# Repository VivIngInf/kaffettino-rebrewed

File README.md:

# ☕ Kaffettino Rebrewed (v2.0)

> Sistema embedded NFC per la gestione automatizzata delle consumazioni, progettato per ambienti reali e scalabilità.

## ☀️ "Buongiornissimo... Arrikaffè!?!?!"

Kaffettino Rebrewed è la **nuova generazione del [progetto Kaffettino](https://github.com/VivIngInf/VivereKaffettino)**: non un semplice aggiornamento, ma una **riscrittura completa** pensata per essere più efficiente, robusta e pronta al futuro.

Se la prima versione era un prototipo brillante, questa è la sua evoluzione:
**hardware custom**, software **modulare** e una filosofia più **industriale**.

## ☕ Cos'è Kaffettino?

Vivere Kaffettino è una **suite** che permette agli utenti dell’Università di Palermo, appartenenti a Vivere Ingegneria, di **segnare le proprie consumazioni** (non solo di caffè) in modo semplice e veloce.

Il sistema è basato su un **ESP32 con lettore NFC**:

- L’utente avvicina la propria card
- Viene verificato il saldo
- Il costo del caffè viene scalato automaticamente

La ricarica viene poi gestita da un amministratore.

## 🤔 Cos’è cambiato con Rebrewed?

Kaffettino Rebrewed nasce come una **reingegnerizzazione completa** del [progetto originale](https://github.com/VivIngInf/VivereKaffettino), mantenendo lo spirito ma **rivoluzionando l’architettura**.

🔧 **Hardware & firmware**:

- PCB custom progettata ad hoc tramite KiCAD
- Firmware completamente riscritto e modularizzato
- Espandibilità grazie a morsettiere per device I2C e SPI
- Pensato per essere replicabile e manutenibile
- Aggiornamenti OTA

🖥️ **Backend**:

- Riscritto tutto il backend in TypeScript
- Integrato con il resto della suite Vivere
- Aggiunto Sito Web allo stack
- Continuazione del bot Telegram già presente nella versione 1

📡 **Connettività intelligente**:

- Riconnessione automatica
- Captive portal per configurazione WiFi
- Antenna esterna per maggiore copertura

🧯 **Gestione errori**:

- Sistema strutturato di gestione errori
- Debug più semplice
- Distinzione tra errori (bloccanti) e warning

## 🧱 Architettura

Kaffettino Rebrewed è composto da:

- ESP32 → legge NFC e comunica con backend
- Backend → gestisce utenti, saldo e logiche
- Web App → interfaccia admin ed utente per statistiche e gestione
- Bot Telegram → interazioni rapide

Tutti i **componenti** comunicano tramite **API REST**.

## 📚 Documentazione

La **documentazione** (utente e amministrativa) è disponibile nella **cartella Docs**.

## 📁 Struttura REPO

> WIP! 🚧

## 🖼️ Image Gallery

> WIP! 🚧

## ♥️ Credits

Realizzato **con amore**, debug e decisamente **troppa caffeina** dai ragazzi di Vivere Ingegneria Dev Hub

<table>
  <tr>
      <th>Daniele Susino</th>
      <th>Antonio Murabito</th>      
  </tr>
  <tr>
      <td></td>
      <td></td>
  </tr>
  <tr>
      <td>Embedded</td>
      <td>Full Stack</td>
  </tr>
  <tr>
      <td>
         <a href="https://www.instagram.com/_antonio.jar/">Instagram 📸</a><br>
         <a href="https://www.linkedin.com/in/susinodaniele/">LinkedIn 👔</a><br>         
         <a href="https://www.susino.dev">Sito 🌐</a>
      </td>
      <td>
         <a href="https://www.instagram.com/_antonio.jar/">Instagram 📸</a><br>
         <a href="https://www.linkedin.com/in/z3ros4n/">LinkedIn 👔</a><br>         
         <a href="https://www.msworks.it">Sito 🌐</a>
       </td>
  </tr>
</table>

---

Si ringrazia, per l'aiuto dato, Nicolas Bruno di [Objex Labs](https://objexlabs.com/)
<br>
Basato su: [Vivere Kaffettino](https://github.com/VivIngInf/VivereKaffettino)

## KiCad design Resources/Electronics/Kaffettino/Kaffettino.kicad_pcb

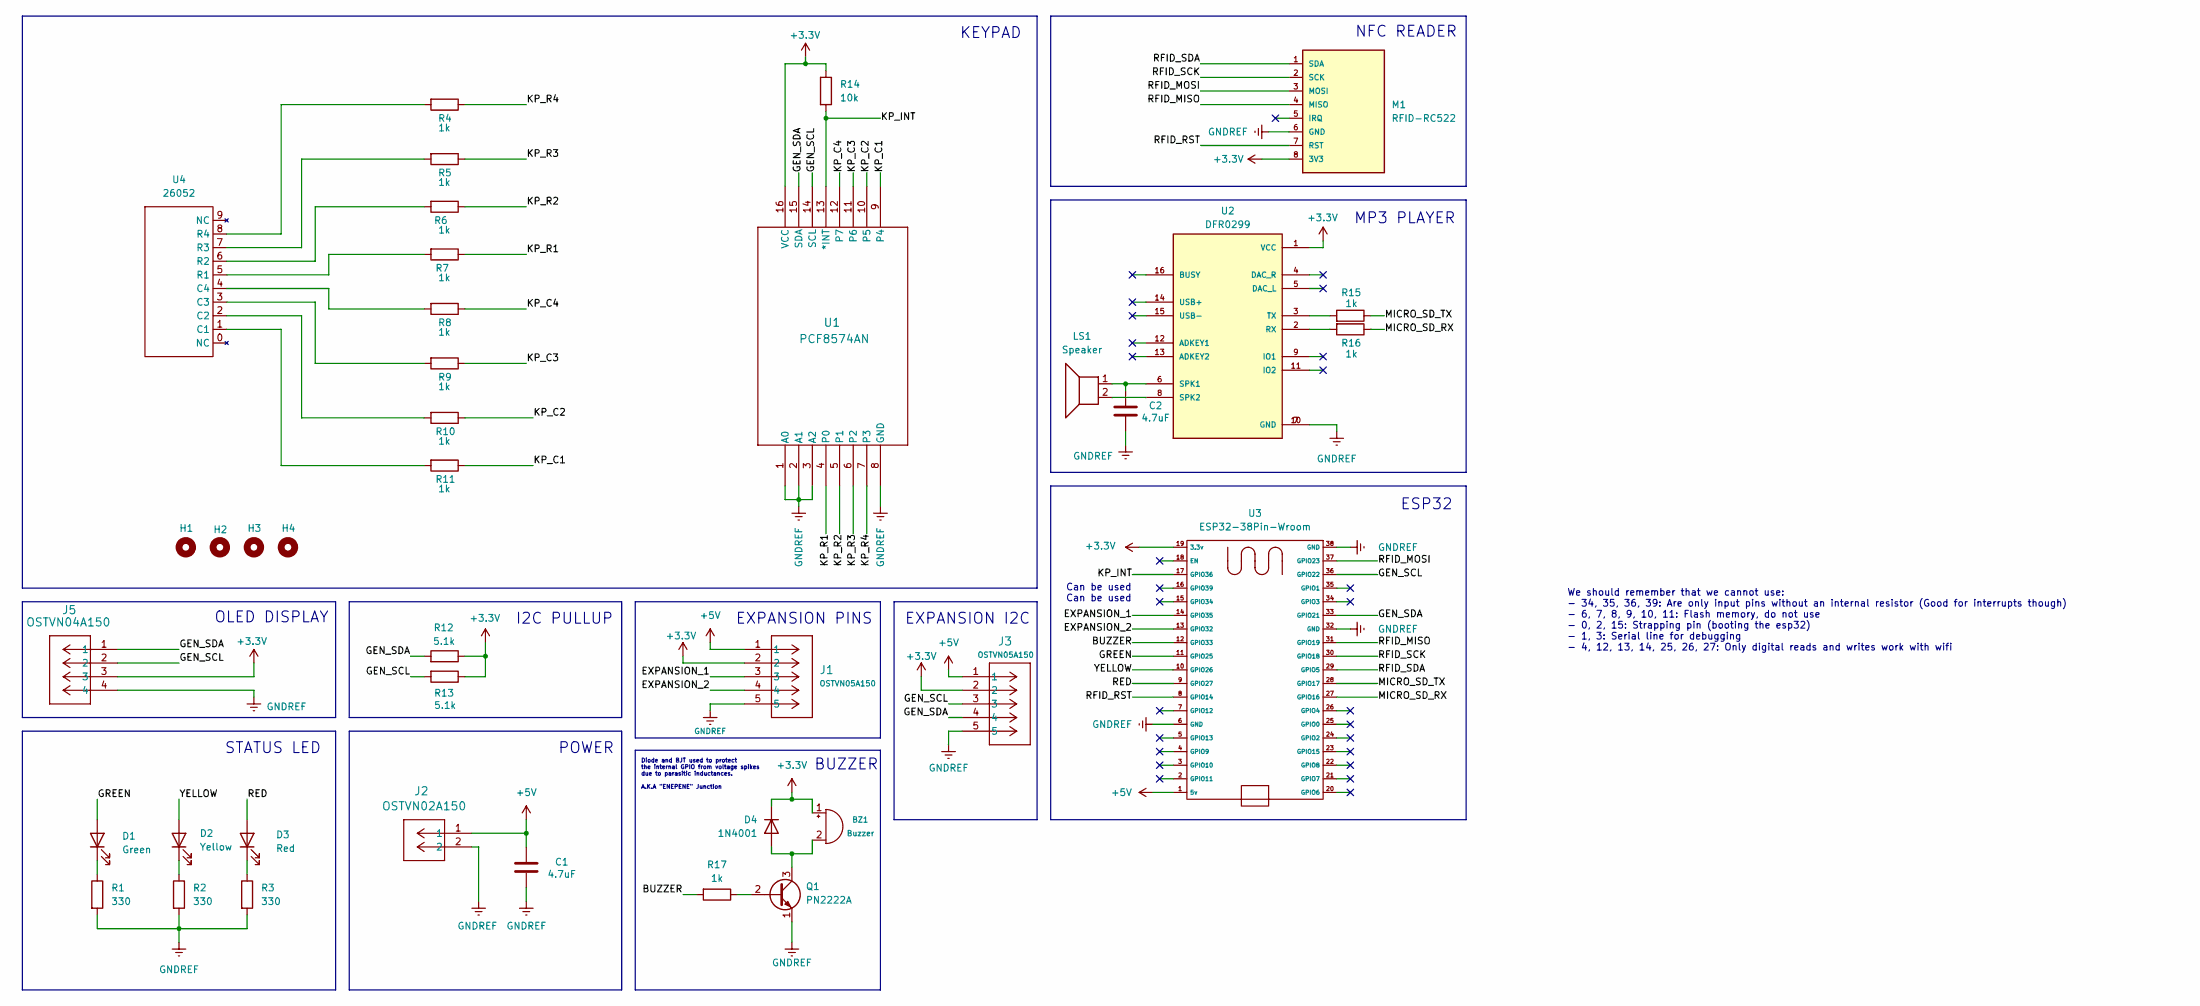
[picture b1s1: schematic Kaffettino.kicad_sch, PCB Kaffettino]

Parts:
BZ1: Buzzer; Buzzer_12x9.5RM7.6
C1, C2: 4.7uF; CP_Radial_D6.3mm_P2.50mm
D1: Green; LED_D5.0mm
D2: Yellow; LED_D5.0mm
D3: Red; LED_D5.0mm
D4: 1N4001; D_DO-41_SOD81_P10.16mm_Horizontal
H1, H2, H3, H4: MountingHole; MountingHole_3.2mm_M3
J1, J3: OSTVN05A150; CONN5_516x256_OST
J2: OSTVN02A150; CONN_OSTVN02A150_OST
J5: OSTVN04A150; CONN_OSTVN04A150_OST
LS1: Speaker; CONN_OSTVN02A150_OST
M1: RFID-RC522; MPN RFID-RC522
Q1: PN2222A; TO-92_Inline
R1, R2, R3: 330; R_Axial_DIN0207_L6.3mm_D2.5mm_P10.16mm_Horizontal
R4, R5, R6, R7, R8, R9, R10, R11, R15, R16, R17: 1k; R_Axial_DIN0207_L6.3mm_D2.5mm_P10.16mm_Horizontal
R12, R13: 5.1k; R_Axial_DIN0207_L6.3mm_D2.5mm_P10.16mm_Horizontal
R14: 10k; R_Axial_DIN0207_L6.3mm_D2.5mm_P10.16mm_Horizontal
U1: PCF8574AN; N16
U2: DFR0299; MODULE_DFR0299
U3: ESP32-38Pin-Wroom; ESP32_38pin
U4: 26052; 26052 matrix keypad 4x4

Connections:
+3.3V: BZ1.1 (+), D4.1 (K), J1.2, J3.2, J5.3, M1.8 (3V3), R12.1, R13.1, R14.1, U1.16 (VCC), U2.1 (VCC), U3.19 (3.3v)
+5V: C1.1, J1.1, J2.1, J3.1, U3.1 (5v)
/BUZZER: R17.2, U3.12 (GPIO33)
/EXPANSION_1: J1.3, U3.14 (GPIO35)
/EXPANSION_2: J1.4, U3.13 (GPIO32)
/GEN_SCL: J3.3, J5.2, R13.2, U1.14 (SCL), U3.36 (GPIO22)
/GEN_SDA: J3.4, J5.1, R12.2, U1.15 (SDA), U3.33 (GPIO21)
/GREEN: D1.2 (A), U3.11 (GPIO25)
/KP_C1: R11.1, U1.9 (P4)
/KP_C2: R10.1, U1.10 (P5)
/KP_C3: R9.1, U1.11 (P6)
/KP_C4: R8.1, U1.12 (P7)
/KP_INT: R14.2, U1.13 (*INT), U3.17 (GPIO36)
/KP_R1: R7.1, U1.4 (P0)
/KP_R2: R6.1, U1.5 (P1)
/KP_R3: R5.1, U1.6 (P2)
/KP_R4: R4.1, U1.7 (P3)
/MICRO_SD_RX: R16.1, U3.27 (GPIO16)
/MICRO_SD_TX: R15.1, U3.28 (GPIO17)
/RED: D3.2 (A), U3.9 (GPIO27)
/RFID_MISO: M1.4 (MISO), U3.31 (GPIO19)
/RFID_MOSI: M1.3 (MOSI), U3.37 (GPIO23)
/RFID_RST: M1.7 (RST), U3.8 (GPIO14)
/RFID_SCK: M1.2 (SCK), U3.30 (GPIO18)
/RFID_SDA: M1.1 (SDA), U3.29 (GPIO5)
/YELLOW: D2.2 (A), U3.10 (GPIO26)
GNDREF: C1.2, C2.2, J1.5, J2.2, J3.5, J5.4, M1.6 (GND), Q1.1 (E), R1.2, R2.2, R3.2, U1.1 (A0), U1.2 (A1), U1.3 (A2), U1.8 (GND), U2.7 (GND), U2.10 (GND), U3.6 (GND), U3.32 (GND), U3.38 (GND)
unnamed: BZ1.2 (-), D4.2 (A), Q1.3 (C)
unnamed: D1.1 (K), R1.1
unnamed: D2.1 (K), R2.1
unnamed: D3.1 (K), R3.1
unnamed: Q1.2 (B), R17.1
unnamed: R16.2, U2.2 (RX)
unnamed: C2.1, LS1.1, U2.6 (SPK1)
unnamed: LS1.2, U2.8 (SPK2)
unnamed: R15.2, U2.3 (TX)
unnamed: R11.2, U4.1 (C1)
unnamed: R10.2, U4.2 (C2)
unnamed: R9.2, U4.3 (C3)
unnamed: R8.2, U4.4 (C4)
unnamed: R7.2, U4.5 (R1)
unnamed: R6.2, U4.6 (R2)
unnamed: R5.2, U4.7 (R3)
unnamed: R4.2, U4.8 (R4)

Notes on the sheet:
Can be used
EXPANSION PINS
KEYPAD
EXPANSION I2C
BUZZER
ESP32
I2C PULLUP
STATUS LED
NFC READER
Diode and BJT used to protect the internal GPIO from voltage spikes due to parasitic inductances. A.K.A "ENEPENE" Junction
POWER
We should remember that we cannot use: - 34, 35, 36, 39: Are only input pins without an internal resistor (Good for interrupts though) - 6, 7, 8, 9, 10, 11: Flash memory, do not use - 0, 2, 15: Strapping pin (booting the esp32) - 1, 3: Serial line for debugging - 4, 12, 13, 14, 25, 26, 27: Only dig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
OLED DISPLAY
MP3 PLAYER

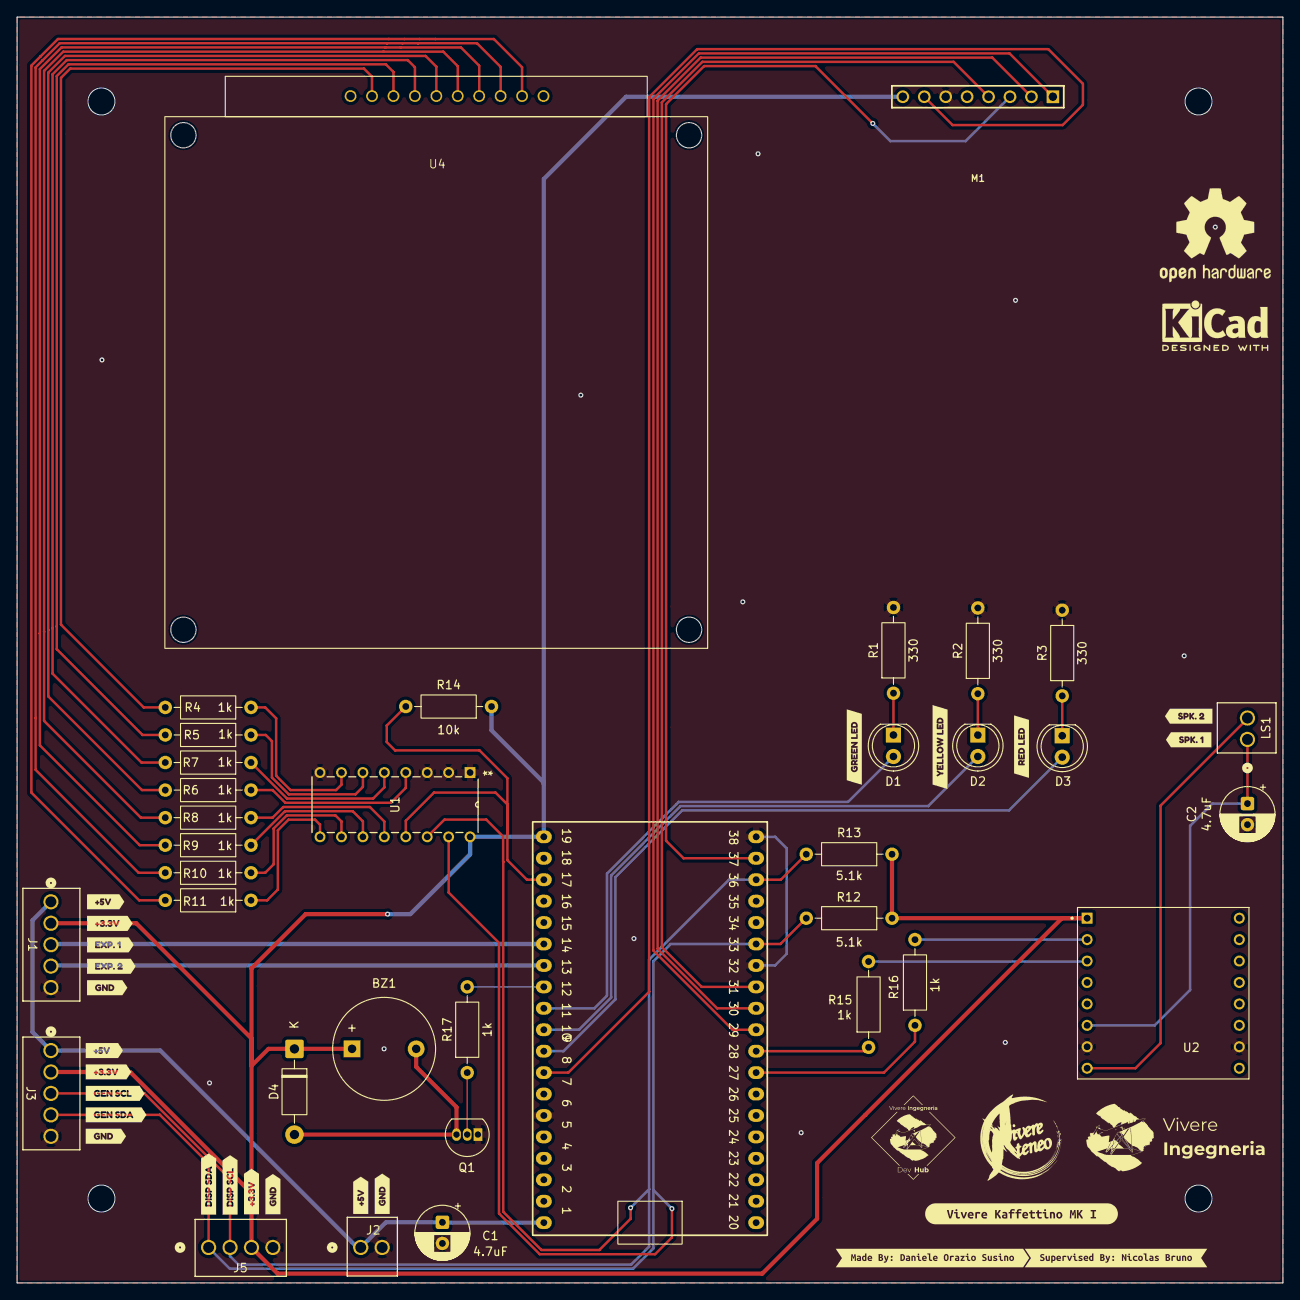
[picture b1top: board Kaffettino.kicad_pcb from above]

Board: 2 copper layers, 149.9 x 149.9 mm, 63 parts (0 on the bottom side), 44 nets.

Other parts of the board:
kibuzzard-69A1A9EC: G***; kibuzzard-69A1A9EC
kibuzzard-69A1A9F8: G***; kibuzzard-69A1A9F8
kibuzzard-69A1A68F: G***; kibuzzard-69A1A68F
kibuzzard-69A1A69C: G***; kibuzzard-69A1A69C
kibuzzard-69A1A695: G***; kibuzzard-69A1A695
kibuzzard-69A1AA1D: G***; kibuzzard-69A1AA1D
kibuzzard-69A1AA2F: G***; kibuzzard-69A1AA2F
kibuzzard-69A1AA21: G***; kibuzzard-69A1AA21
kibuzzard-69A1AA26: G***; kibuzzard-69A1AA26
kibuzzard-69A1AA29: G***; kibuzzard-69A1AA29
kibuzzard-69A1AA32: G***; kibuzzard-69A1AA32
kibuzzard-69A1AB1B: G***; kibuzzard-69A1AB1B
kibuzzard-69A1AB21: G***; kibuzzard-69A1AB21
kibuzzard-69A1ABEC: G***; kibuzzard-69A1ABEC
kibuzzard-69A1AC2A: G***; kibuzzard-69A1AC2A
kibuzzard-69A1AC24: G***; kibuzzard-69A1AC24
kibuzzard-69A1B1F4: G***; kibuzzard-69A1B1F4
kibuzzard-69A1B1FA: G***; kibuzzard-69A1B1FA
kibuzzard-69A1B2CD, kibuzzard-69A1B2CD#2: G***; kibuzzard-69A1B2CD
kibuzzard-69A86FC7: G***; kibuzzard-69A86FC7
kibuzzard-69A188C8: G***; kibuzzard-69A188C8
kibuzzard-69A188E1: G***; kibuzzard-69A188E1
kibuzzard-69A188E6: G***; kibuzzard-69A188E6

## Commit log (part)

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2025-11-16 Corrected some footprints in the PCB schema
2025-11-18 Add wallet request feature and related endpoints
    Introduces the WalletRequest model and RequestStatus enum in the Prisma schema to support wallet creation requests. Adds new API endpoints for users to request wallet creation and for admins/treasure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
2025-11-20 Add wallet and top-up search with pagination support
    Introduces utility types for pagination and range search, and updates wallet routes to support filtered and paginated queries for wallets and top-ups. Implements corresponding handler methods to fetc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
2025-11-25 Add wallet top-up endpoint and handler stub
    Introduced a POST /wallet/topup route with input validation and user wallet checks. Added a stub for the topUp method in wallet-handler.ts to support future implementation of wallet top-up functional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
2025-11-26 Refactor TopUp model and implement wallet top-up logic
    Removed user and auletta relations from the TopUp model in schema.prisma. Updated wallet top-up API to accept an optional description and implemented the topUp method in wallet-handler to create a To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
2025-11-26 Add device API scaffolding and update wallet topup
    Introduces initial scaffolding for device-related API endpoints, including a request decorator and middleware. Also updates the wallet topup endpoint to require a description field in the request pay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
2025-11-28 Started working on Fallback website that changes configs and stores them in the memory of the ESP
2025-11-28 Refactor inventory schema and handler methods
    Renamed 'marginPrice' to 'price' in the Inventory model for clarity. Updated InventoryHandler methods to better reflect item and product operations, added method decorators, and improved method namin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
2025-11-28 Upgrade Prisma to v7 and update dependencies
    Upgraded @prisma/client and prisma to version 7.0.1, updated related dependencies, and added new dev dependencies for Prisma development and AST parsing. Also added prisma.config.ts and made changes 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
2025-11-29 Embedded: Config html completed, connectivity lacks failback in case it randomly drops.
2025-11-29 Add name field and unique constraint to Inventory
    Introduces a 'name' field to the Inventory model in the Prisma schema and enforces uniqueness. Updates InventoryHandler to support inventory creation with a name and refactors method signatures to us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
2025-11-29 Embedded: Fallback to webserver if cannot connect to WiFi.
2025-11-29 Add Vitest configuration and update test scripts
    Introduced Vitest for testing by adding vitest.config.ts and updating package.json scripts. Added related devDependencies for Vitest, coverage, UI, and Vite integration to support improved testing wo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
2025-12-02 Set the webserver to be always avaiable
2025-12-02 Fixed a missplaced lable in electrical schema
2025-12-03 NFC Reader interrupt
2025-12-03 Embedded: Added Captive Portal
2025-12-04 Refactor device registration and error handling
    Updated Prisma schema to make device fields optional and removed DeviceLog model. Enhanced device registration flow to check for verified devices and pending requests, and added new utility methods f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
2025-12-04 Add endpoint to accept device registration requests
    Introduces a PUT /device endpoint restricted to admins for accepting device registration requests. Updates error messages and improves parameter validation for device registration.
2025-12-07 Add device API key management and middleware
    Introduces device API key generation, validation, and authorization logic in device-handler. Adds device middleware for API key authentication, updates request/response structures in device routes, a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
2025-12-07 Update device registration flow and status handling
    Renamed RequestStatus enum value from SENT_TO_CLIENT to AWAITING_CLIENT and updated all related logic and references. Improved device registration endpoint to check for AWAITING_CLIENT status, added 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
2025-12-09 Add card and aulette handlers, extend device API
    Introduced card and aulette handler utilities, middleware for card validation, and new device API endpoints for aulette, inventory, and wallets. Updated Fastify request types to include card informat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
2025-12-12 Add card API routes and refactor imports to ESM
    Introduces new /card API endpoints for creating cards and updating card PINs, including validation and permission checks. Refactors all internal imports to use explicit ESM '.js' extensions and updat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
2025-12-14 Working mp3 player, oled screen and nfc scanner
2025-12-14 Embedded: Added Buzzer and LED support
2025-12-14 Add card block/unblock functionality and API endpoints
    Introduces a 'blocked' field to the Card model and adds logic to block or unblock cards via new API endpoints. Middleware and card handler are updated to enforce blocked status, returning an error if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
2025-12-16 Add product retrieval and improve product endpoints
    Introduced a new GET endpoint to retrieve a product by ID and refactored product creation and update endpoints for consistency. Added error handling for missing products and standardized API response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
2025-12-25 Refactor handler imports and add audit logging
    Consolidates all handler imports under a new utils/handlers directory and updates all references accordingly. Introduces a new AuditLog model in the Prisma schema and adds a utility for audit logging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
2025-12-25 Refactor response handler imports and usage
    Moved response-handler.ts to handlers/ directory and updated all imports accordingly. Centralized sendError and sendSuccess exports in handlers.ts for cleaner imports. Updated route handlers to consi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
2025-12-25 Refactor middleware imports with central mws module
    Introduced a new mws.ts file to re-export commonly used middleware. Updated all route files to import middleware from the new central module, reducing import duplication and improving maintainability.
2025-12-25 Add audit logging to API route handlers
    Introduced auditLog calls to card, device, inventory, user, and wallet route handlers to record key actions such as creation, updates, and transactions. This enhances traceability and accountability 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
2025-12-27 Initialize Next.js app for vivere-services
    Set up a new Next.js project in the vivere-services directory with initial configuration files, dependencies, ESLint, Tailwind CSS, and example assets. Includes base README, .gitignore, and starter a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
2025-12-30 Update backend API dependencies and middleware
    Added bun.lock for Bun package management and updated package.json dependencies. Refactored and updated multiple middleware, plugin, route, handler, and utility files to improve authentication, permi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
2025-12-30 Switch kaffettino to Bun, update dependencies
    Replaced npm's package-lock.json with bun.lock for both the root and kaffettino directories, updated package.json dependencies, and adjusted .gitignore. Updated Prisma configuration and schema files 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
2026-01-07 Trying images on display and almost finished PCB design.
2026-01-07 Finished routing in PCB, waiting for approval
2026-01-07 Add Swagger to backend and restructure frontend for i18n
    Integrated @fastify/swagger into the backend API with a new plugin and updated dependencies. Refactored frontend Next.js app to support locale-based routing and layouts, added i18n utilities, and rem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
2026-01-08 Add deployment workflow and PM2 config
    Introduces a GitHub Actions workflow for deploying to a VPS via SSH on push to main, and adds a PM2 ecosystem configuration for managing the kaffettino-api-server process using Bun.
2026-01-08 Refactor device route and update env vars in config
    Removed mandatory 'location' param check from the device route and adjusted aulette handler to handle undefined locations. Also added new environment variables to ecosystem.config.js for improved con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
2026-01-10 Add UI components and update homepage layout
    Introduced new UI components (badge, button, card, drawer, input, separator, textarea, etc.) and a ServiceCard component for the homepage. Updated the homepage layout to showcase services with a new 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
2026-01-11 Add OpenAPI schemas and Swagger UI for card routes
    Introduces detailed OpenAPI schema definitions for all card-related endpoints, including request/response validation and documentation tags. Updates the Swagger plugin with project-specific metadata,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
2026-01-12 anto's problems
2026-01-18 Add troubleshooting section and adjust card title size
    Introduced a troubleshooting section to the locale page to assist users with service access issues. Also updated the ServiceCard component to use a smaller title font size for better visual consisten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
2026-01-23 Embedded: Added critical error message
2026-01-23 Embedded: Started error handleing
2026-01-23 Embedded: handled all init errors, differentiated between warnings and errors
2026-01-24 Embedded: created a custom logging utility, migrated all logging to new framework
2026-02-03 Embedded: Don't rember lmao
2026-02-04 Embedded: Improved connection script, added connection errors, started dynamic WiFi selection in HTML.
2026-02-08 Add Course model, update auth and frontend auth
    Add a Course model to Prisma and link it to User (courseId relation with SetNull on delete, unique name, timestamps). Expose courseId in the backend auth configuration. Add frontend auth pages and co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
2026-02-08 Support multiple CORS origins; enable signup
    Allow multiple origins in the backend CORS plugin (uses CLIENT_ORIGIN or http://localhost:6969 and adds http://localhost:3000) via an origin callback to permit local dev from Next.js. Update frontend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
2026-02-09 Export Auth type and update auth client & signup
    Expose the Auth type from the backend auth module and re-export it for consumers (added export in api/src/auth.ts, new shared/auth.ts and backend/packages/auth-types/index.ts). Mark birthDate and cou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
2026-02-09 Auth origins, session cookie fix, signup UI cleanup
    Backend: set auth baseURL to process.env.API_BASE_URL (fallback IP) and expand trustedOrigins to include local Next.js and backend addresses so requests and origin checks match the backend address. F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
2026-02-09 Log cookies and disable secure cookies temporarily
    Print the full cookie header in the Kaffettino layout for debugging and temporarily disable secure cookies in the backend auth client. layout.tsx now logs cookieHeader value to aid troubleshooting; a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
2026-02-09 Add UI components, admin dashboard and deps
    Introduce a set of reusable UI components and utilities and add the admin dashboard page. New components were added under src/components/ui (avatar, breadcrumb, chart, checkbox, dropdown-menu, sheet,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
2026-02-24 Embedded: fixed some footprints in the PCB design, started working on keyEvents.
2026-02-27 Embedded: Finished developing PCB, fixed grb and drill files, added silkscreen.
    TODO: Check correctness of footprints and NPN Junction.
2026-02-27 Embedded: Switched buzzer from 15 (strapping pin) to 33, reflected the changes in the PCB
2026-02-27 Embedded: Incresed size of silkscreen
2026-02-27 Embedded: Forgot to update gbr and drill files
2026-03-04 Add device zod schemas and validate routes
    Introduce zod schemas for device payloads (deviceRegistrationSchema, deviceValidateId, deviceValidateName, deviceValidateNameAndId) and corresponding TypeScript types (IDeviceRegistrationSchema, IDev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
2026-03-04 Fixed wrong PCB label 3.3 to 5V
2026-03-10 Added music files
2026-03-15 Embedded: Fixed some text width so that JLCPCB's DRC won't whine about it
2026-03-22 Addded Banner
2026-03-24 Readme added br in footer
2026-04-05 Add VSCode C/C++ properties and launch
    Add .vscode/c_cpp_properties.json and .vscode/launch.json to configure a Windows GCC/GDB development/debug environment. Update .vscode/settings.json to include C_Cpp_Runner defaults (compiler/debugge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
2026-04-20 Debug Mode, Pragma everywhere, Checks on SPIFFS, removed magic numbers, fixed platformio.ini, added keypad support (thanks claude, will refactor)
2026-04-23 Main Menu on PCB and full PCB models on Kicad, exported on blender
2026-04-24 Export images PCB, created ugly PCB for Samuele (shitty PC)
2026-05-02 Fix error object + created aulette route handler
2026-05-03 error messages showup
2026-05-03 Added Aulette routes
